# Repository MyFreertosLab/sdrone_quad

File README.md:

ESP32 ESP-IDF Drone
===================

This is a Drone Implementation with esp-idf and esp32.
This software is under construction, but it works.

```
  git clone --recursive https://github.com/MyFreertosLab/sdrone_quad.git
  idf.py build
  idf.py flash
```
<h1>The first step</h1>
<p align="left">
  
  <p>Step 1: Minimal Hardware List</p>
</p>

1) The frame
2) RC TX/RX (I use FlySky I-BUS, but works well with PPM also)
3) PPM Encoder (if you not use FlySky I-Bus)
4) IMU (mpu9250) with at least accelerometer and gyroscope
5) Battery
6) Esc (30Ah)
7) Motors
8) Propellers
9) The Board (a simple ESP32 board)
10) Cup of coffee

<h1>The first test</h1>

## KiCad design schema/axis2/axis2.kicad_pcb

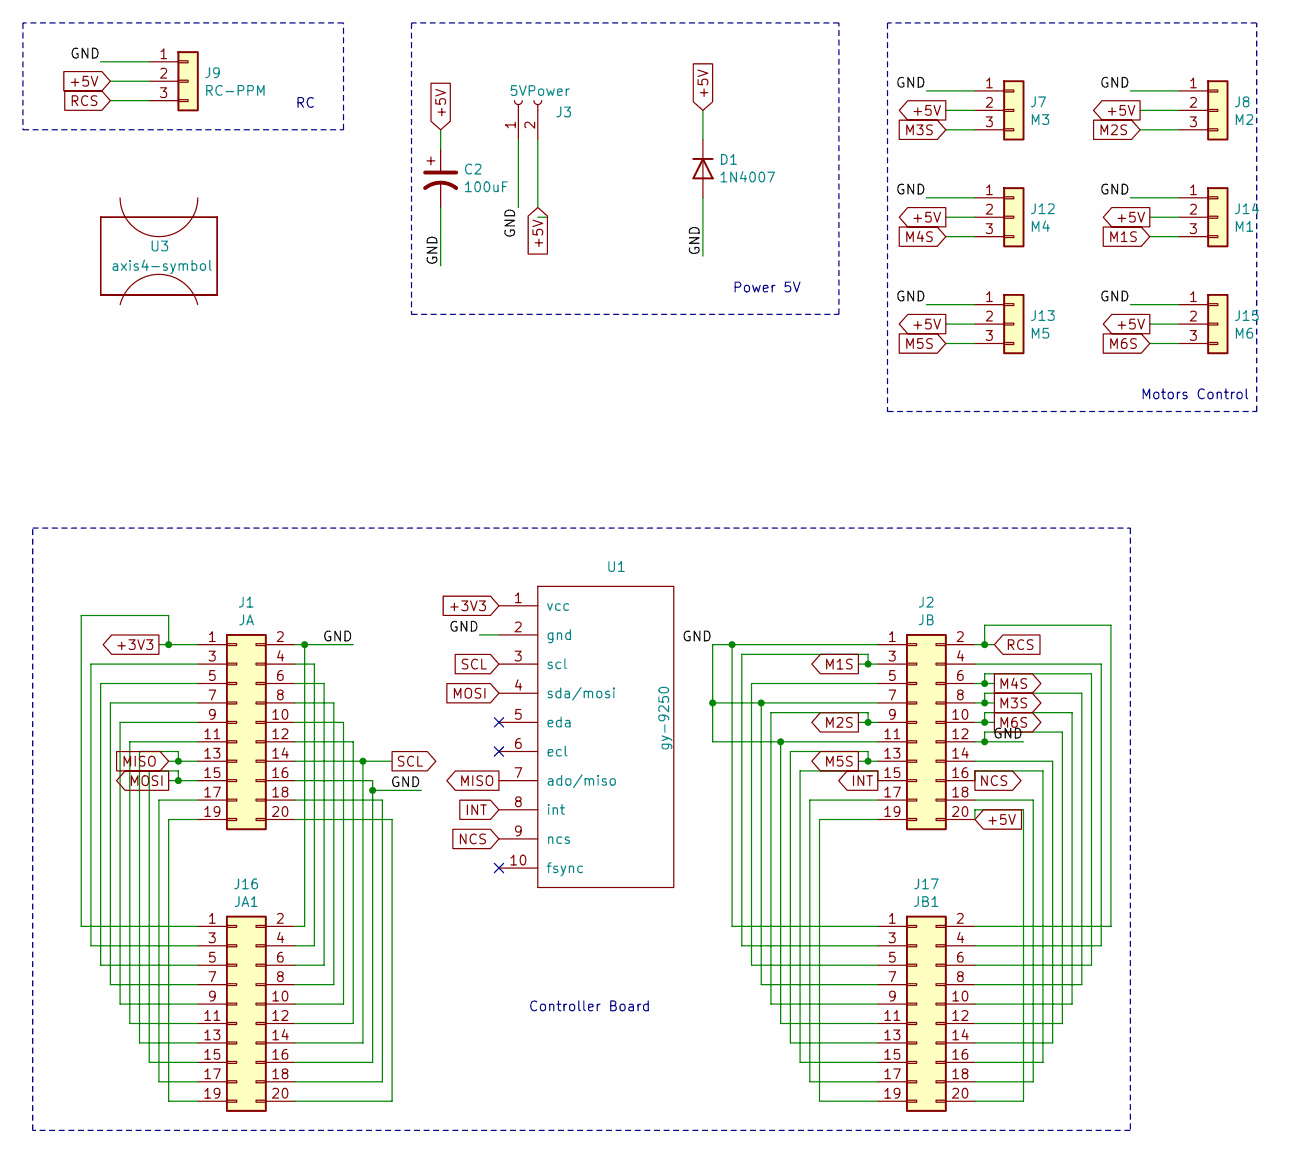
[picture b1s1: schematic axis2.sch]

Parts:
C2: 100uF; CP_Radial_D5.0mm_P2.50mm
D1: 1N4007; D_DO-41_SOD81_P10.16mm_Horizontal
J1: JA; PinSocket_2x10_P2.54mm_Vertical
J2: JB; PinSocket_2x10_P2.54mm_Vertical
J3: 5VPower; JST_XH_B2B-XH-AM_1x02_P2.50mm_Vertical
J7: M3; PinHeader_1x03_P2.54mm_Horizontal
J8: M2; PinHeader_1x03_P2.54mm_Horizontal
J9: RC-PPM; PinHeader_1x03_P2.54mm_Horizontal
J12: M4; PinHeader_1x03_P2.54mm_Horizontal
J13: M5; PinHeader_1x03_P2.54mm_Horizontal
J14: M1; PinHeader_1x03_P2.54mm_Horizontal
J15: M6; PinHeader_1x03_P2.54mm_Horizontal
J16: JA1; PinSocket_2x10_P2.54mm_Vertical
J17: JB1; PinSocket_2x10_P2.54mm_Vertical
U1: gy-9250
U3: axis4-symbol; axis4-frame

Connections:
+3V3: J1.1, J16.1, U1.1 (vcc)
+5V: C2.1, D1.1 (K), J2.20, J3.2, J7.2, J8.2, J9.2, J12.2, J13.2, J14.2, J15.2, J17.20
/GND: C2.2, D1.2 (A), J1.2, J1.16, J2.1, J2.7, J2.11, J2.12, J3.1, J7.1, J8.1, J9.1, J12.1, J13.1, J14.1, J15.1, J16.2, J16.16, J17.1, J17.7, J17.11, J17.12, U1.2 (gnd)
INT: J2.15, J17.15, U1.8 (int)
M1S: J2.3, J14.3, J17.3
M2S: J2.9, J8.3, J17.9
M3S: J2.8, J7.3, J17.8
M4S: J2.6, J12.3, J17.6
M5S: J2.13, J13.3, J17.13
M6S: J2.10, J15.3, J17.10
MISO: J1.13, J16.13, U1.7 (ado/miso)
MOSI: J1.15, J16.15, U1.4 (sda/mosi)
NCS: J2.16, J17.16, U1.9 (ncs)
unnamed: J1.3, J16.3
unnamed: J1.4, J16.4
unnamed: J1.5, J16.5
unnamed: J1.6, J16.6
unnamed: J1.7, J16.7
unnamed: J1.8, J16.8
unnamed: J1.9, J16.9
unnamed: J1.10, J16.10
unnamed: J1.11, J16.11
unnamed: J1.12, J16.12
unnamed: J1.17, J16.17
unnamed: J1.18, J16.18
unnamed: J1.19, J16.19
unnamed: J1.20, J16.20
unnamed: J2.4, J17.4
unnamed: J2.5, J17.5
unnamed: J2.14, J17.14
unnamed: J2.17, J17.17
unnamed: J2.18, J17.18
unnamed: J2.19, J17.19
RCS: J2.2, J9.3, J17.2
SCL: J1.14, J16.14, U1.3 (scl)

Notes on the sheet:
Power 5V
Controller Board
Motors Control

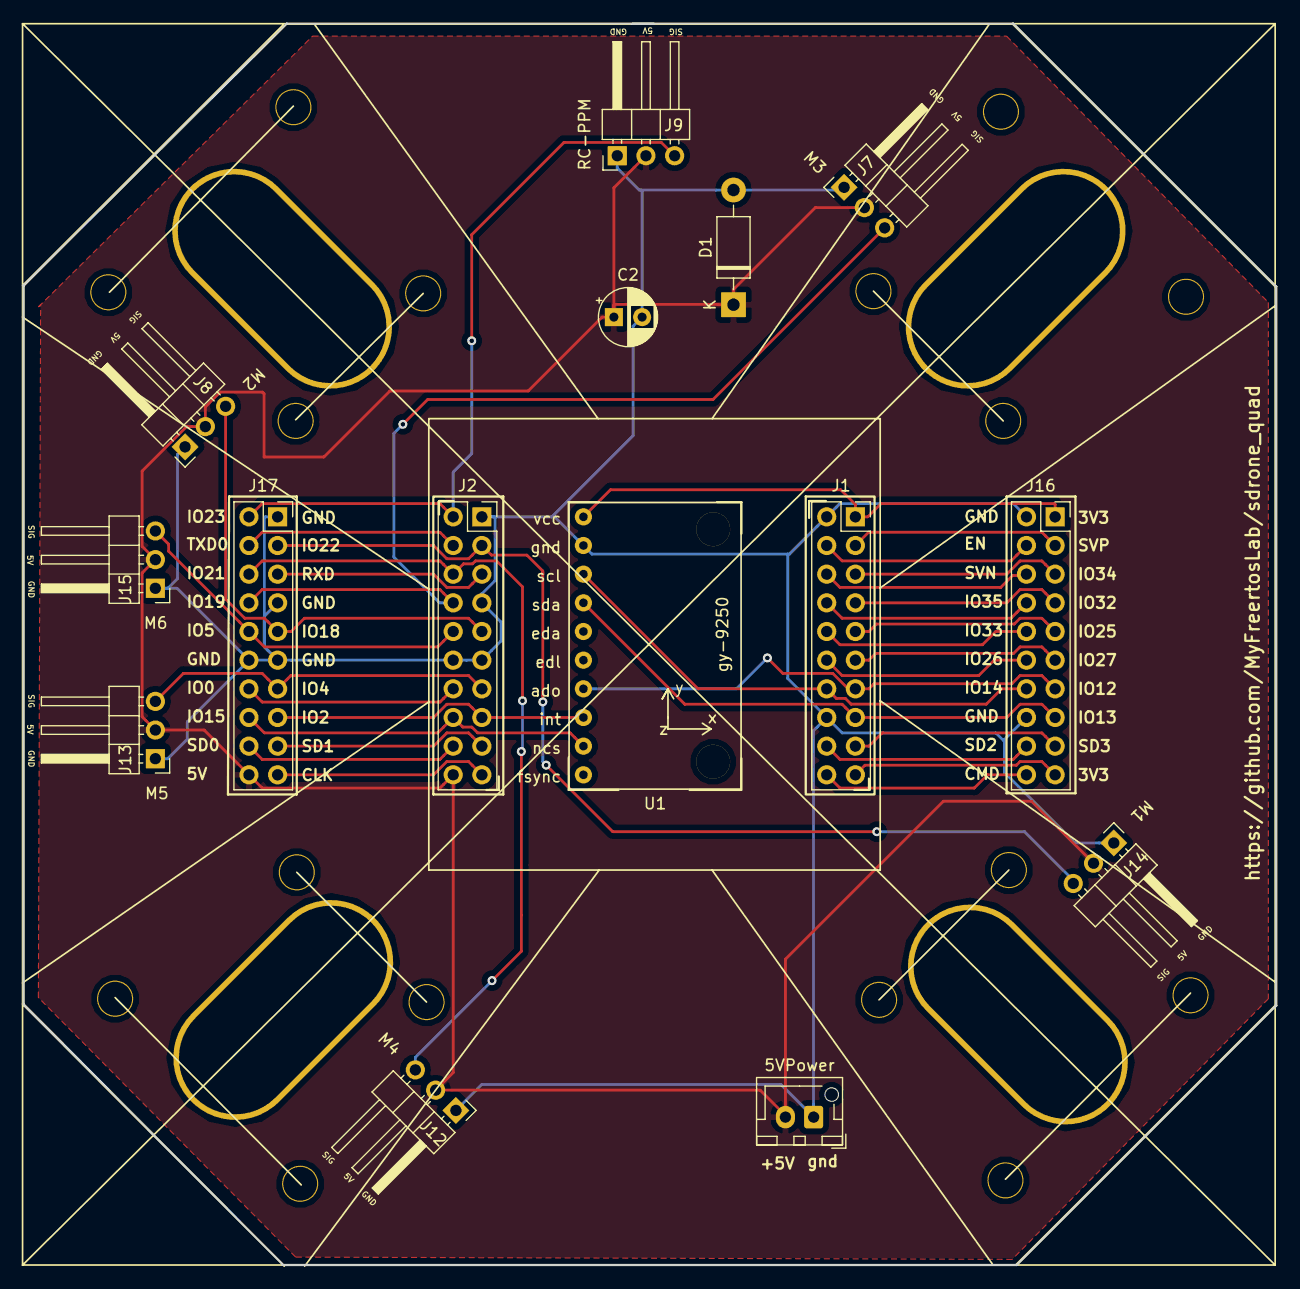
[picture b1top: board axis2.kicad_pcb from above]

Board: 2 copper layers, 111.0 x 110.0 mm, 16 parts (0 on the bottom side), 35 nets.

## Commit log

2021-07-16 Primo commit
2021-07-16 Aggiunto moduli driver
2021-07-16 Aggiunto sdkconfig e gitignore e gitattributes
2021-07-19 Eliminato ciclo di misure
2021-07-19 Iniziato sviluppo quad
2021-08-14 Corretto scheda. Erano invertiti i pin degli headers
2021-09-05 Iniziato sviluppo controller
2021-09-05 Pull drivers
2021-09-06 Input motori: momentum & thrust
2021-09-06 Tolto commento
2021-09-07 Corretto momentum con at
2021-09-07 Limitato W a +- 0.5 rad
2021-09-07 Tolto istruzioni commentate
2021-09-08 Limitato Wz
2021-09-08 Limitato max w per asse z a 2.0f
2021-09-09 Aggiunto at e thrust si stato dei motors
2021-09-11 Aggiunto bozza arm/disarm con gesture rc
2021-09-11 Aggiunto limiti motors in [0,4.4] newton
2021-09-11 force commit
2021-09-11 Il controller corregge l'errore solo se thrust richiesto è maggiore di 2.0 newton
2021-09-15 Tolto alimentazione 12V dalla scheda. Utilizzo alimentazione separata per i motori
2021-09-19 Ridotto ke_z
2021-09-19 Pongo U = 0 in un intorno di RC = 0 per yaw,pitch,roll
2021-09-21 Aggiunto errore integrale e sistemato ke e ki. Volo quasi corretto ...
2021-10-07 Integrato Magnetometer. Da provare
2021-10-09 estratto alcuni metodi
2021-10-18 Aggiunto wifi per supporto telemetria
2021-10-19 Aggiunto websocket per telemetria
2021-10-19 Eliminato zero intorno agli stick dell'RC
2021-11-01 Inizio studio accelerazioni
2021-11-01 Aggiunto script di formattazione sci dei dati di volo
2021-11-13 Calcolo dinamico zero accelerometro (per ora ad eliche ferme) e modificato range Thrust (-200,200)
2021-11-19 Aggiunto thrust nello stato X e nell'uscita Y
2021-11-21 Corretto condizione di attivazione della correzione e abbassato KE,KI
2021-11-22 Aggiunto offset per motori ed aggiunto evento di telemetria per soli dati z
2021-11-25 Messo a zero offset motori
2021-11-30 Bozza transizioni di stato sdrone e controllo accelerazione Z
2021-12-04 Aggiunto bozza conversioni geometriche accelerazioni e calcolo errori
2021-12-04 rimesso integrale errori per RPY, ma non per accel
2021-12-05 Iniziato prove di volo con controllo velocità veticale
2021-12-10 sostituito vertical_v con speed_if e implementato bozza riconoscimento 'atterrato'
2021-12-10 Aggiunto yaw_reference in sdrone_state ed aggiunto possibilità di disabilitare correzioni yaw, pitch, roll ed acc per permettere i test su ogni asse separatamente
2021-12-17 no buono ...
2021-12-17 ke e ki acc orizzontali azzerati, mentre ke e ki asse verticale aggiornati con valori corretti
2021-12-19 Per ora correggo solo accelerazione verticale in Y
2021-12-19 Iniziato refactoring wsserver
2021-12-20 Corretto calcolo accelerazioni richieste
2021-12-21 Aggiornato telemetria con wsserver ed eseguito rpove di volo
2022-04-17 Corretto Readme
2022-04-30 Inizio ad aggiungere barometro
